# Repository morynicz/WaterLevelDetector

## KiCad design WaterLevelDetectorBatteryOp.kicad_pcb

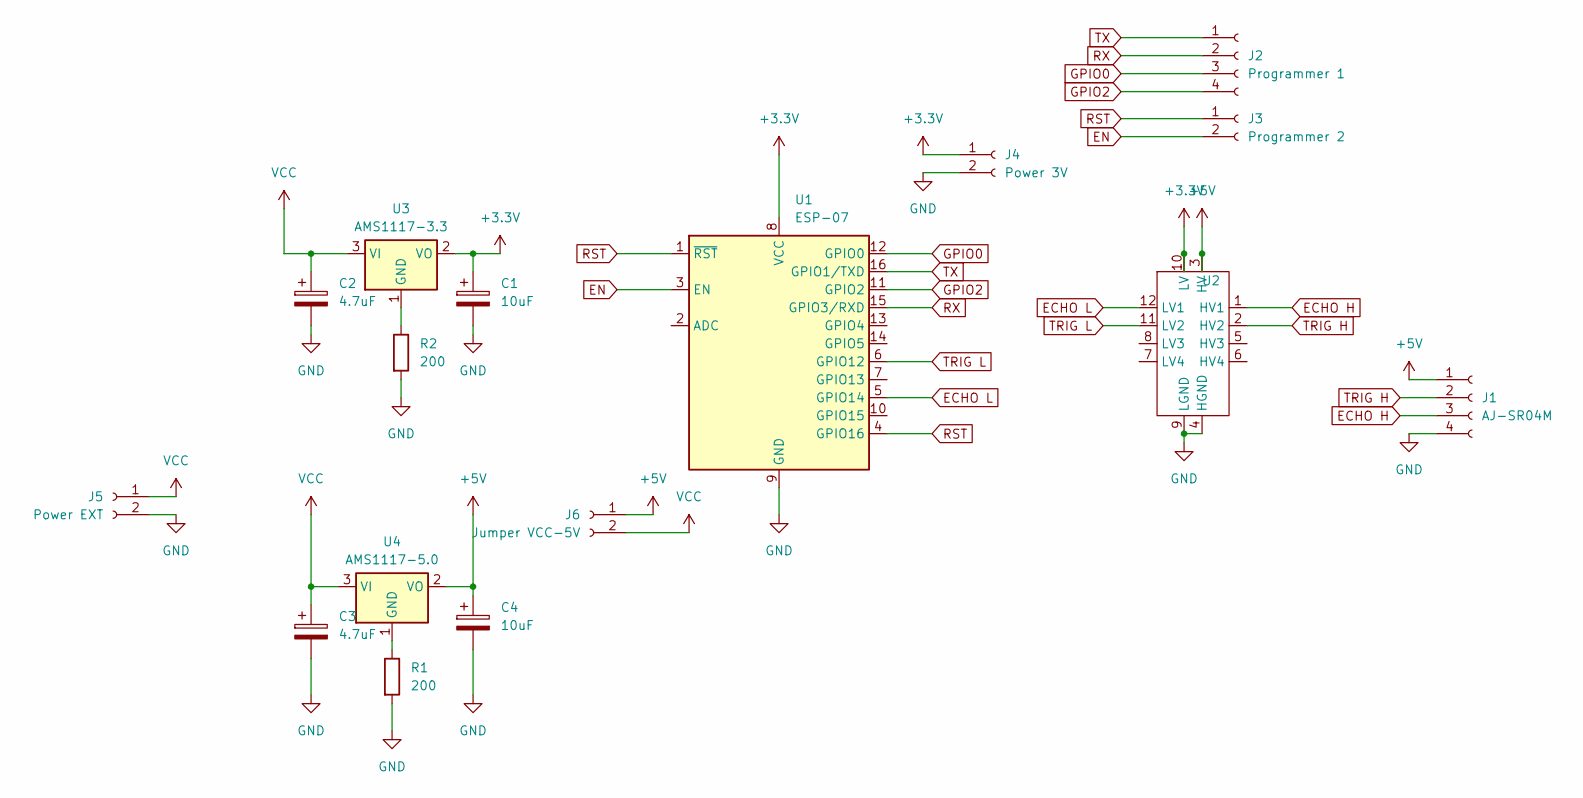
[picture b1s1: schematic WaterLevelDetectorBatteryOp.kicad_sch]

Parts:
C1, C4: 10uF; C_0805_2012Metric
C2, C3: 4.7uF; C_1206_3216Metric
J1: AJ-SR04M; PinSocket_1x04_P2.54mm_Vertical
J2: Programmer 1; PinSocket_1x04_P2.54mm_Vertical
J3: Programmer 2; PinSocket_1x02_P2.54mm_Vertical
J4: Power 3V; PinSocket_1x02_P2.54mm_Vertical
J5: Power EXT; PinSocket_1x02_P2.54mm_Vertical
J6: Jumper VCC-5V; PinSocket_1x02_P2.54mm_Vertical
R1, R2: 200; R_0805_2012Metric
U1: ESP-07
U2: LogicLevelConverter_4CH
U3: AMS1117-3.3; SOT-223-3_TabPin2
U4: AMS1117-5.0; SOT-223-3_TabPin2

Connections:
+3.3V: C1.1, J4.1, U1.8 (VCC), U2.10 (LV), U3.2 (VO)
+5V: C4.1, J1.1, J6.1, U2.3 (HV), U4.2 (VO)
ECHO H: J1.3, U2.1 (HV1)
ECHO L: U1.5 (GPIO14), U2.12 (LV1)
EN: J3.2, U1.3 (EN)
GND: C1.2, C2.2, C3.2, C4.2, J1.4, J4.2, J5.2, R1.2, R2.2, U1.9 (GND), U2.4 (HGND), U2.9 (LGND)
GPIO0: J2.3, U1.12 (GPIO0)
GPIO2: J2.4, U1.11 (GPIO2)
unnamed: R2.1, U3.1 (GND)
unnamed: R1.1, U4.1 (GND)
RST: J3.1, U1.1 (~RST), U1.4 (GPIO16)
RX: J2.2, U1.15 (GPIO3/RXD)
TRIG H: J1.2, U2.2 (HV2)
TRIG L: U1.6 (GPIO12), U2.11 (LV2)
TX: J2.1, U1.16 (GPIO1/TXD)
VCC: C2.1, C3.1, J5.1, J6.2, U3.3 (VI), U4.3 (VI)

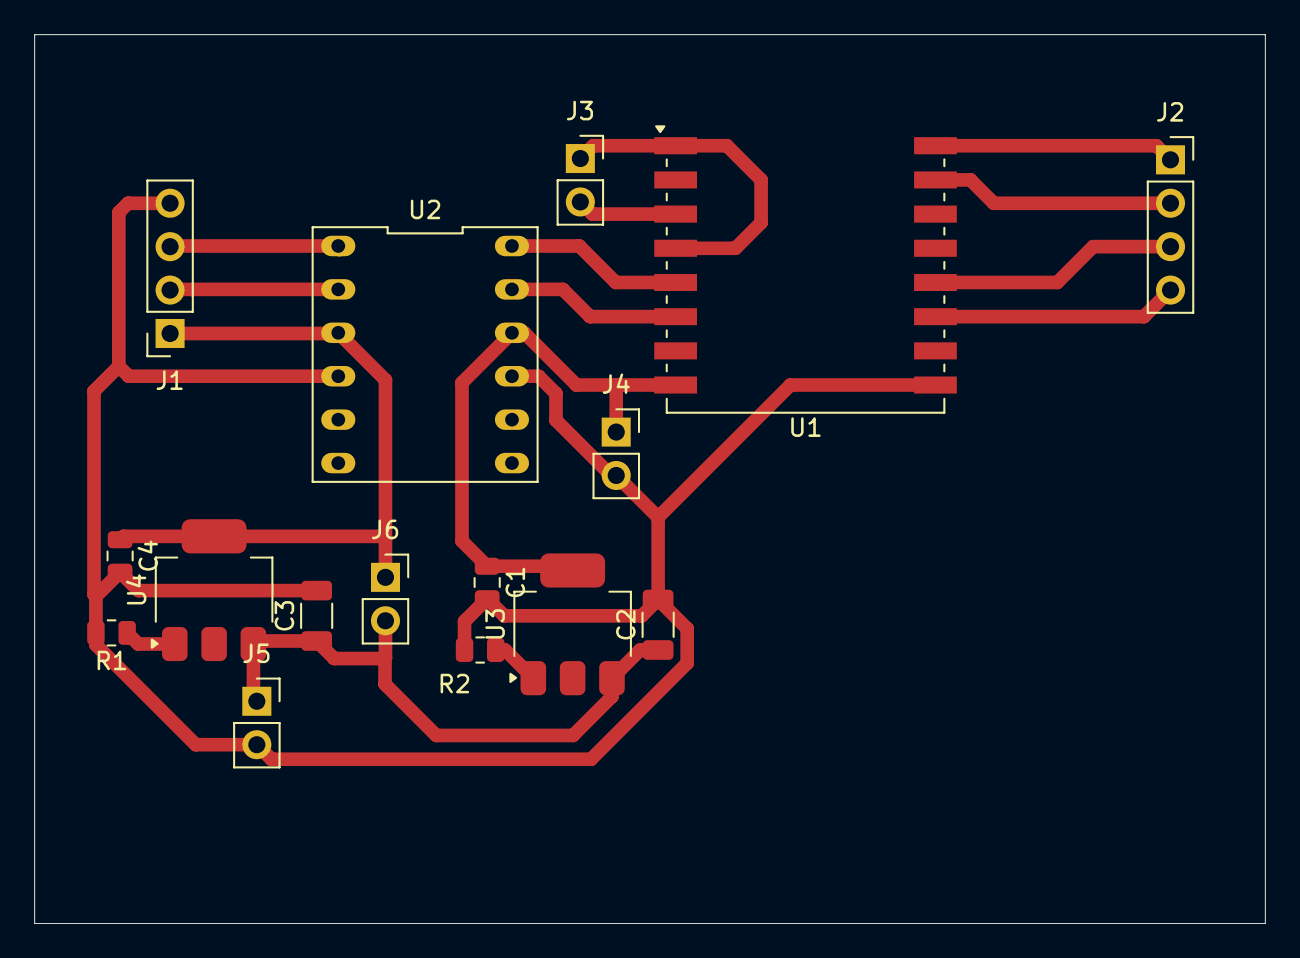
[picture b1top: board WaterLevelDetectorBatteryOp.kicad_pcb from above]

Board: 2 copper layers, 72.0 x 52.0 mm, 16 parts (0 on the bottom side), 16 nets.
